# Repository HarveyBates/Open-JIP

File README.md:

### Description

Open-JIP is an open-source chlorophyll *a* fluorometer used to quantify photosynthetic phenotypes in terrestrial plants and microalgae. It is controlled via a Teensy microcontroller and features highly customisable electrical components and a 3D-printed infrastructure. 

#### OJIP

Open-JIP utilises a technique known as the fast polyphasic rise fluorescence
(also known as OJIP). Steady irradiance is provided from an emitting LED, this
excites photosynthetic antenna in the sample resulting in excess irradiance
being emitted as photons of a longer wavelength (i.e. fluorescence). The
emitted fluorescence, which contains information regarding the state of
photosynthesis, is captured by a photodiode, amplified by the custom circuitry
and stored by the Teensy microcontroller. This all happens in less than a second.

The transient captured by Open-JIP gives the user an indication of the state of photosynthesis in the subject organism to varying levels of complexity. If you would like to know more about the theory surrounding the measurement of chlorophyll *a* fluorescence, this [link](https://doi.org/10.1016/j.algal.2020.102105) gives a basic introduction and resources for further reading.

### Publication

The original device which used an Arduino Mega was published in [Photosynthesis Research in 2019](https://doi.org/10.1007/s11120-019-00673-2):

*A guide to Open-JIP, a low-cost open-source chlorophyll fluorometer - Bates et al. 2019*

If you would like to see what the device is capable of, you may be interested in this recent [publication](https://doi.org/10.1016/j.algal.2020.102105) which uses Open-JIP as a flow-through chlorophyll *a* fluorometer connected [a custom photobioreactor](https://github.com/HarveyBates/Phenobottle) with the microalga *Chlorella vulgaris*.

### Collaborations and custom architecture 

If you would like to collaborate on a project, or would like to see if Open-JIP can be customised to suit your application, please email me at [harvey_bates@hotmail.com](mailto:harvey_bates@hotmail.com). 

### Disclaimer

Open-JIP requires some knowledge of electronics, programming and photosynthesis to operate. If you have problems with the device place an issue in the [issues](https://github.com/HarveyBates/Open-JIP/issues) tab of this repository and I will do my best to address it as soon as possible.

# USER MANUAL

Below contains the user manual for Open-JIP, if you have any questions there is a discussions tab in this github repository, where I will do my best to get back to you as soon as possible.

## Contents

1. Introduction
   1. Specifications
   2. Getting started
      1. Downloading files
         1. Method 1 (New users)
         2. Method 2 (Experienced users / collaborators)
      2. Gathering materials
         1. Printed circuit board (PCB)
            1. Ordering a PCB
         2. 3D models
         3. Additonal parts
2. Firmware / Software
   1. Introduction
   2. Arduino IDE / Teensyduino
   3. Basic operations
      1. Basic functions
      2. Advanced functions
      3. Calibration functions
   4. Python control
   5. Advanced operations
      1. Change actinic LED intensity
      2. Change detection sensitivity
      3. Set analog reference voltage & Resolution
      4. Defaults
      5. Length of actinic pulse
3. Hardware
   1. Detection
      1. Gain adjustment 
   2. Actinic Intensity

## 1. Introduction

### Specifications

| Feature            | Value / Description                                          |
| ------------------ | ------------------------------------------------------------ |
| Actinic LED Colors | **Blue** 455 – 485 nm (466 nm), **Green** 517 – 555 nm (532 nm), **Orange** 583 – 600 nm (593 nm), **Red** 617 – 635 nm (626 nm). |
| Resolution         | 10 to 16-bit (optimised for 12-bit)                          |
| Sampling rate      | 8 &mu;s at 12-bits                                           |
| Operating voltage  | 15 V 1.2 A (Barrel plug)                                     |
| Communications     | USB (Serial)                                                 |
| Microcontroller    | Teensy 3.5/3.6 or Teensy 4.1 (3.6 Recommended)               |
| Actinic Intensity  | Four intensities (Low, Mid, High, Very High)                 |
| Detection (Gain)   | Four settings (Low, Mid, High, Very High)                    |

### Getting started

#### Downloading files

##### Method 1 (New users)

New users should navigate to the [releases](https://github.com/HarveyBates/Open-JIP/releases) page to find the most recent (and stable) version of the device. You can download the latest release as a `.zip` file and this will contain all the files you need to get the device up and running. 

The most recent version is **v0.3**. 

When searching through files in this repository all relevant folders are labeled with a specific version. You will want to use files that match the version you are using.

##### Method 2 (Experienced users / collaborators)

If you want to contribute to the project or fork this directory feel free to do so, just know that I constantly update files here so they may not function as expected before release. 

To clone this directory type this into your terminal / console.

```bash
git clone https://github.com/HarveyBates/Open-JIP.git
```

#### Gathering materials

Open-JIP can be built in an afternoon if you have all the equipment at hand. The folder "Bill of Materials" contains all the materials needed to build Open-JIP. This has been divided into two parts; (1) circuit board and (2) other. 

In addition to the Bill of Materials you will need to have access to:

1. A soldering iron
2. Solder (Paste or wire variety)
3. A re-flow oven (not necessary but makes the circuit board easier to assemble)
4. A 3D-printer
5. A pair of wire strippers / cutters
6. Some tweezers

##### Printed circuit board (PCB)

In the ```Bill of Materials/Circuit Board``` folder you will find a table all the components needed to construct the Open-JIP circuit board. These components can be bought from common electronics suppliers such as [digikey](https://www.digikey.com/), [LCSC](https://lcsc.com/en) or [farnell](https://au.element14.com/) etc. Links for each component is provided.

Note that most of the components are surface mount (SMD), this is due to their increased reliability and in my opinion its easier to assemble SMD compared to through-hole (THT) components. 

###### Ordering a PCB

To order the circuit board I recommend using [JLCPCB](https://jlcpcb.com/) as they are cheap, easy and ship fast. 

1. Open the folder titled Electronics 
2. Navigate to your current version 
3. In the subdirectory select the folder containing gerber and drl files
4. Compress this folder into a ```.zip``` file. 
5. On the JLCPCB website drag and drop the ```.zip``` file into the order form. 

The default settings are suitable. 

##### 3D Models

The 3D-models used for 3D-printing Open-JIP can be found in the ```Open-JIP/Hardware``` folder. Two file types are specified:

1. ```.stl``` can be directly imported into 3D-printing software such as [Ultimaker-Cura](https://ultimaker.com/software/ultimaker-cura) or sent to a local 3D-printing manufacturer.
2. ```.STEP``` is the modifiable Open-JIP 3D-model and as such can be configured whichever way you want before being exported as a ```.stl``` file. You can use 3D modeling software to do this such as [Fusion360](https://www.autodesk.com/products/fusion-360/overview) or [Solidworks](https://www.solidworks.com/).

##### Additional parts

In addition to the above electronics you will need a few components such as a Teensy microcontroller, power supply, computer to use the device etc. A table of all these additional items can be found in the folder location ```Bill of Materials/Other```.

## 2. Firmware / Software

### Introduction

Open-JIP operates via a computers serial port (USB connection), the user sends commands in the form of strings that are read by the Teensy microcontroller. This results in the device taking a measurement or other tasks. You can do this manually though the Arduino IDE or by using scripts in various languages. 

### Arduino IDE / Teensyduino

To setup the Teensy (upload the firmware to the microcontroller) you will need **both** [Arduino IDE](https://www.arduino.cc/en/software) and [TeensyDuino](https://www.pjrc.com/teensy/teensyduino.html) if running on Linux or Windows, or just [TeensyDuino](https://www.pjrc.com/teensy/teensyduino.html) if using a Mac. Instructions on how to do this is provided in the above links. 

When first using Open-JIP: 

1. Plug the Teensy into your computer
2. Open Arduino IDE
3. Select ```Tools>Board>Teensy 3.6``` (may be in another part called Teensyduino)
4. Select ```Port>"Your Teensy Device"```
5. ```File>Open``` the "Teensy.ino" file found in ```Firmware/v0.3/Teensy_3.6/Teensy_3.6.ino```
6. ```Sketch>Upload``` to flash the file onto the Teensy

The provided ```Teensy.ino``` file will work as is, but if you wish to change settings in this file you will need to reupload the firmware to the Teensy again after changes have been made.

### Basic Operations

To take a measurement open the serial monitor (in the Arduino IDE when the device is connected to your computer) (```Tools>Serial Monitor```) and type in the command ```MF``` (denoting **m**easure **f**luorescence). This will (in the default configuration) take a one second measurement of chlorophyll *a* fluorescence and print the resulting measurements out into the serial monitor. You can copy and paste the data into excel in order to graph the transient.

There are a number of included functions that require the same method to operate:

#### Basic functions

1. ```MF``` - **M**easure fluorescence. Measure the chlorophyll *a* fluorescence signature of the organism of interest. 
2. ```CP``` - **C**alculate **p**arameters. Calculate and print out basic fluorescence parameters from the most recent OJIP curve. 
3. ```CFo``` - **C**alibrate **F<sub>o</sub>** (the minimum level fluoresence). Provides short flashes of illumination for calibrating the minimum level fluorescence. This command is useful if you want to know if your measurement is going to *saturate* (due to an overly concentrated sample) before taking a measurement. 
4. ```An``` - **A**ctinic intensity (irradiance of LED) where *n* is a number between 1 and 4 (lowest to highest).
5. ```Fn``` - **F**luorescence gain (sensitivity of detection) where *n* is a number between 1 and 4 (lowest to highest).

**Note** - It is recommended that the minimum level of fluorescence (F<sub>o</sub>) is greater than 0.3 V for the maximum stability of acquisitions.

#### Advanced functions

1. ```MJ``` - **M**easure **J**-step. Measures up to the J-step (~2 ms) and returns the data to the serial port.
2. ```MW``` - **M**easure **w**ave. Measures up to the J-step multiple times with set time intervals between acquisitions. 

#### Calibration functions

1. ```ML``` - Calibrate actinic intensity (**m**easure **l**ight). Turns on the actinic LED for a period of three seconds to allow the intensity to be measured by a 4&#960; light meter.
2. ```Cr``` **C**alibrate **r**ise time of the actinic LED/amplifier combination. Provides some short  (100us) flashes of illumination from the actinic LED to calibrate your setup using an external oscilloscope. Useful if you want to ensure your Fo value is accurate (i.e. Fo should be measured when the actinic LED and amplifier are stable (usually around 40us)). *Note* this is only nessesary if you alter the default electronics configuration (see below).  

### Python Control

Open-JIP comes with an external cross platform python script that allows users to take basic measurements, plot the data and sort it into a ```.csv``` file automatically. This program is located under ```External Control/Open-JIP.py```.

```Open-JIP.py``` uses [plotly](https://plotly.com/python/) to plot the data and [pyserial](https://pyserial.readthedocs.io/en/latest/pyserial.html) to access the serial port of your machine. You must have [python](https://www.python.org/) installed to use this script. **This program runs in the terminal / console**. Additonally you need pip to install these requirements as follows:

```bash
cd Open-JIP/Software
pip3 install -r requirements.txt
python3 Open-JIP.py
# or (depending on python installation)
pip install -r requirements.txt
python Open-JIP.py
```

If you wish to change the output path of the ```.csv``` file you can do so by changing this string in ```Open-JIP.py```:

```python
fileName = "Open-JIP_Data.csv"  # Filename of output .csv file
```

### Advanced operations

A major feature of Open-JIP is its customisability. In the firmware users can adjust:

1. The actinic LED intensity
2. The detection sensitivity
3. The analog reference voltage
4. Resolution of the device
5. Length of actinic pulse

This next section is going to be in reference to the files located within ```Firmware/v0.3/Teensy_3.6```.

#### Change actinic LED intensity

In ```actinic.cpp``` the actinic LED intensity can be adjusted. There are four possible configurations, LOW, MID, HIGH, VERY HIGH. These can be selected by applying the values 1 - 4 (LOW - VERY HIGH) when switching on the actinic LED. 

```C++
void Actinic::on(){
  switch(intensity){
    case 1:
      digitalWrite(actinicGain1, HIGH); // Low
    	break;
    case 2:
      digitalWrite(actinicGain2, HIGH); // Mid
      break;
    case 3:
      digitalWrite(actinicGain3, HIGH); // High
      break;
    case 4:
      digitalWrite(actinicGain4, HIGH); // Very high
      break;
  }
}
```

*Note-* Electrical components have intrinsic variability. If using identical devices ensure actinic intensity is similar using a PAR meter.

*DO NOT -* combine actinic LED intensities as this will result in undefined behaviour. 

#### Change detection sensitivity

In ```sensitivity.cpp``` the detection sensitivity can be adjusted. There are four possible detection configurations, LOW, MID, HIGH, VERY HIGH (1 - 4). These are set before starting an exposure for stability and are therefore defined by the user.

```C++
void Sensitivity::define(int _gain){
    refresh();
    switch(_gain){
        case 1:
            // Lowest
            digitalWrite(fluoroGain1, HIGH); // Photosynthesis (OJIP)
            break;
        case 2:
            digitalWrite(fluoroGain2, HIGH); // Photosynthesis (OJIP)
            break;
        case 3:
            digitalWrite(fluoroGain3, HIGH); // Concentration only (not recommended for photosynthesis)
            break;
        case 4:
            // Highest
            digitalWrite(fluoroGain4, HIGH); // Concentration only (not recommended for photosynthesis)
            break;
    }
}
```
**NOTE**

Recent testing of the gain settings of Open-JIP has led to the conclusion that the current version of the device (v0.3) can only use gain 1 and 2 for photosynthesis (OJIP) measurements. Gain 3 and 4 should only be used for concentration estimates using the fluorescence intensity at ~120 &mu;s.

 *DO NOT* - combine gain settings as this will result in undefined behaviour. 

#### Set analog reference voltage & Resolution

In ```fluorescence.cpp``` the reference voltage can be adjusted to either 3.3 or 1.1 volts when using a Teensy 3.6. The purpose of this is (1) the Teensy 3.6 (1.1 V) reference voltage is more stable than 3.3 V and (2) you can attain a higher resolution when measuring weak fluorescence signals.

```C++
void Fluorescence::set_reference_voltage(float voltage){
  // Sets and initialises the required reference voltage for measurements
  if(voltage == 3.3){
    analogReference(DEFAULT); // Set to 3.3 V
  }
  else if(voltage == 1.1){
    analogReference(INTERNAL1V1); // Set to 1.1 V
  }
  else{
    analogReference(DEFAULT); // Set to default (3.3 V) if unknown value is found
  }
  analogRead(readPin); // Initialise reference voltage
}
```

*Note* - This is usually done statically at the start of the program by adjusting the value of ```refVoltage``` to either 3.3 or 1.1 depending on your requirements.

The number of bits for each reading can be changed via this command in the ```void setup()``` function:

```c++
analogResolution(12); // 12-bit resolution
```

*Note* - **Increasing** the resolution **decreases** the sampling rate so if you want to get alot of data points around Fo I reccomend you use a 12 or 10-bit resolution.

If you use have a 12 bit-resolution with a reference voltage of 1.1V the finest sensivitiy of the device is 0.00027 V per-division (1.1V / 2<sup>12</sup>) at a 8 &mu;s sampling rate. 

#### Defaults

Upon startup, Open-JIP will revert to its default configuration. You can change this by altering the setup command in ```Teensy_3.6.ino```:

```C++
void setup() {
  Serial.begin(115200); // Starting baud rate
  analogReadResolution(12); // Default resolution
  pinMode(13, OUTPUT); // Sets the microcontrollers LED pin as an output
  
  sensitivity.refresh(); // Switch off all sensitivity settings
  sensitivity.define(1); // Set a default sensitivity (1 - 4)

  actinic.off(); // Switch off all actinic settings
  actinic.define(1); // Set a default actinic irradiance (1 - 4)
}
```

#### Length of actinic pulse

In ```fluorescence.h``` the length of the actinic exposure (pulse) can be adjusted. The acquisition is done in two steps; (1) the fast measurments (readings every 8 &mu;s) and (2) slow (readings every 1 ms). These arrays require different processing methods and are therefore stored seperately. Below gives you an idea of how the array lengths are calculated for the intial aqusitions and the converted output. 

```c++
// Microsecond (micro) = readings every 8 us
static const unsigned int microLength = 1000; 
int microRead [microLength];
int milliRead[microLength];

// Millisecond (milli) = readings every 1 ms
static const unsigned int milliLength = 1000; 
int microTime[milliLength]; 
int milliTime[milliLength];

// Stores final array in converted form (i.e. Volts and Milliseconds)
float fluorescenceValues[microLength + milliLength];
float timeStamps[microLength + milliLength];
```

*Note* - If you are using the ```Open-JIP.py``` script you will need to change the number of data points that are read to match the length of ```fluorescenceValues```:

```python
timeStamps, fluorescenceValues = measure_fluorescence(2000) # Match with teensy script array length (default 2000)
```

## 3. Hardware

Open-JIP operates using a Teensy 3.6 microcontroller connected to a custom printed circuit board (PCB). The circuit is divided into two parts:

1. Detection - Responsible for detecting emitted fluorescence
2. Actinic intensity - Responsible for turning on and off the actinic LED

### Detection

Fluorescence detection is achieved with the use of an operational amplifier (op-amp) connected as a transimpedance amplifier. The inverting input is connected to a photodiode, while the non-inverting input is connected to a voltage divider to provide a very small offset voltage. The concept of the offset voltage is that the amplifier (op-amp) will respond faster to changes in voltage. 

*Note-* Resistor values may change depending on your application.

#### Gain adjustment

Four different sensitivities are provided though the use of a CMOS switch (74HC4066D) which has a range of different feedback resistors (1M, 2M, 3.3M and 3.9M). These resistors are all 0805 SMD. The gain is selected in the firmware of Open-JIP; however, if you wish to adjust the senstivity futher you can do so by changing one or more of these resistors. 

**Increasing** the resistance of the feedback resistor will **increase** the sensitivty of detection.

**Decreasing** the resistance of the feedback resistor will **decrese** the sensitivty of detection.

**Note**

Feedback resistances above 2Mohm are not suitable for OJIP measurements in v0.3. Ideally the feedback resistor should be a small as possible to increase the response time of the device.

**Note**

If you begin to get a large overshoot occurring at the start of your measurements you may need to increase the capacitor value (C3) to 2pF - 5pF. This [article](https://wiki.analog.com/university/courses/electronics/electronics-lab-1st) may help you if you encounter this issue.

### Actinic intensity

The actinic LED is controlled in the same way as the detection circuit i.e. Using a CMOS switch to controll its brightness. Again four levels of brightness can be selected in the firmware and are controlled by resistors (10K, 12K, 15K, 20k) connected to the base of the darlington transisitor (BD681). Adjusting the value of these resistors will result in the LED getting brighter or dimmer based on their resistance value.

*Note-* Resistor values may change depending on your application.

The input voltage (15 V) is filtered through a 12 V linear voltage regulator. This regulator ensures the actinic LED is stable of the measurement. A small capacitor (C7 - 1 &mu;F) is placed across the LED's terminal to prevent overshoot. If you want the LED to respond faster you can reduce the value of this capacitor while using an oscilloscope to check the devices rise-time. 

**Increasing** the resistors results in **decreased** actinic brightness.

**Decreasing** the resistance of R10 results in **increased** actinic brightness.

**Note**

Gate resistor values are dependent on a number of factors including manufacturer tolerances and LED color. Dialing in the resistor values to use in your device is an important consideration. Typically you will need a PAR meter to calibrate the devices brightness before use (if using for OJIP measurements). However, if access to a PAR meter is an issue, the shape of the OJIP curve can be an indicator of LED intensity. If the rise between Fo and Fj is sharp and rapid (<2ms), typically the device has enough brightness to saturate the electron transport chain. However, if the rise between Fo and Fj is gradual (>2ms), the brightness may not be bright enough. 

## Future of Open-JIP

Since the publication of Open-JIP a number of changes have been made to increase the devices capabilities. These include:

1. ~~Adjustable fluorescence protocols~~

2. ~~Ability to change detection sensitivity dynamically (though software)~~

3. ~~Adjustment of actinic LED intensity dynamically (through software)~~
4. Improvements in resolution
5. Improvements in number of datapoints in each OJIP transient

## Licence

The software in this work is licensed under GNU AFFERO GENERAL PUBLIC LICENSE Copyright (C) (2020) (Harvey Bates)

This program is free software: you can redistribute it and/or modify it under the terms of the GNU General Public License as published by the Free Software Foundation, either version 3 of the License, or (at your option) any later version.

This program is distributed in the hope that it will be useful, but WITHOUT ANY WARRANTY; without even the implied warranty of MERCHANTABILITY or FITNESS FOR A PARTICULAR PURPOSE. See the GNU General Public License for more details.

You should have received a copy of the GNU General Public License along with this program. If not, see https://www.gnu.org/licenses/

For more information contact: [harvey_bates@hotmail.com](mailto:harvey_bates@hotmail.com)

The hardware (3D Models, Electronic Schematics) in this work is licensed under a [Creative Commons Attribution-ShareAlike 3.0 Unported License](http://creativecommons.org/licenses/by-sa/3.0/).

[https://doi.org/10.1016/j.algal.2020.102105]: 
[https://pyserial.readthedocs.io/en/latest/pyserial.html]:

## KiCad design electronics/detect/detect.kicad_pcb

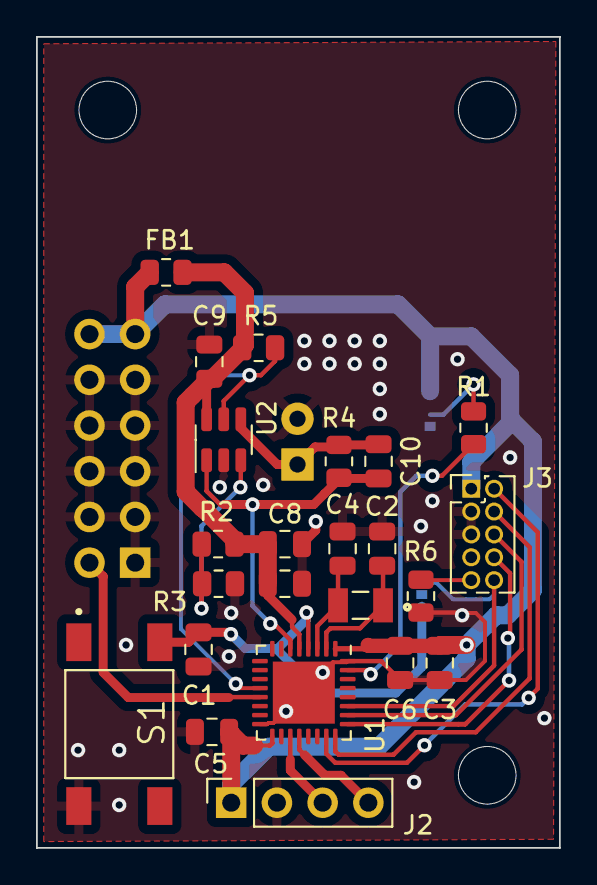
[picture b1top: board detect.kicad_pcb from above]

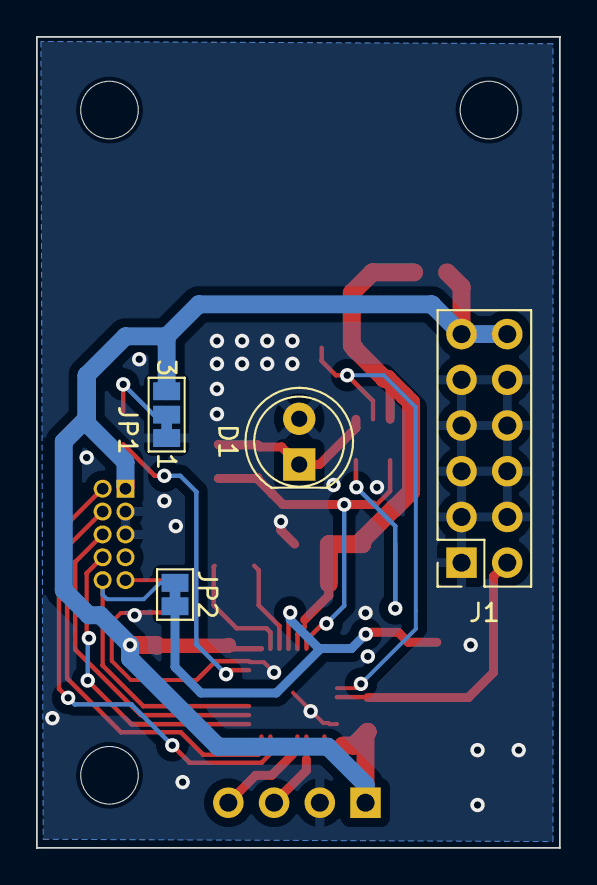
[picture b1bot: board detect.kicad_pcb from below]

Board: 2 copper layers, 29.1 x 45.1 mm, 27 parts (4 on the bottom side), 21 nets.

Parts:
C1, C3, C5, C9: 100nF; C_0805_2012Metric
C2, C4: 10pF; C_0805_2012Metric
C6: 4.7uF; C_0805_2012Metric
C7: 1uF; C_0805_2012Metric
C8: 10nF; C_0805_2012Metric
C10: 0.1pF; C_0805_2012Metric
D1: SFH213FA; LED_D5.0mm_IRGrey
FB1: R_0805_2012Metric
J1: Conn_02x06_Counter_Clockwise; PinSocket_2x06_P2.54mm_Vertical
J2: Conn_01x04_Socket; PinSocket_1x04_P2.54mm_Vertical
J3: Conn_ARM_JTAG_SWD_10; PinHeader_2x05_P1.27mm_Vertical
JP1: Boot_Sel; SolderJumper-3_P1.3mm_Bridged12_Pad1.0x1.5mm_NumberLabels
JP2: SolderJumper-2_P1.3mm_Bridged_Pad1.0x1.5mm
R1, R6: 10K; R_0805_2012Metric
R2: 1M; R_0805_2012Metric
R3: 33K; R_0805_2012Metric
R4: 500K; R_0805_2012Metric
R5: 100K; R_0805_2012Metric
S1: RESET; TL3301AF160QG
U1: STM32L432KCU6; QFN-32-1EP_5x5mm_P0.5mm_EP3.45x3.45mm
U2: OPA328DBVR; SOT-23-6
Y1: ECS-.327-12.5-34R-C-TR

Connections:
+3.3V: C3.1, C5.1, C6.1, FB1.2, J1.11, J1.12, J2.1, J3.1 (VTref), JP1.3 (B), U1.1 (VDD), U1.17 (VDD)
/ADC1_IN5: C10.2, R4.2, U1.6 (PA0), U2.1
/BOOT_SELECT: R1.2, U1.31 (PH3)
/PA6: R5.2, U1.12 (PA6), U2.5 (EN)
/PA7: J1.2, U1.13 (PA7)
/TCK/SWCLK_PA14: J3.4 (SWDCLK/TCK), U1.24 (PA14)
/TDI_PA15: J3.8 (NC/TDI), U1.25 (PA15)
/TDO/SWO_PB3: J3.6 (SWO/TDO), U1.26 (PB3)
/TMS/SWDAT_PA13: J3.2 (SWDIO/TMS), U1.23 (PA13)
/TRST_PB4: J3.10 (~RESET), JP2.1 (A), U1.27 (PB4)
/USART1_RX: J2.4, U1.20 (PA10)
/USART1_TX: J2.3, U1.19 (PA9)
GND: C1.2, C2.2, C3.2, C4.2, C5.2, C6.2, C7.2, C8.2, C9.2, D1.2 (A), J1.1, J1.3, J1.4, J1.5, J1.6, J1.7, J1.8, J1.9, J1.10, J2.2, J3.3 (GND), J3.5 (GND), JP1.1 (A), R3.2, R6.2, S1.2, U1.16 (VSS), U1.32 (VSS), U1.33 (VSS), U2.2 (V-)
NRST: C1.1, JP2.2 (B), S1.3, U1.4 (NRST)
unnamed: C10.1, D1.1 (K), R4.1, U2.4 (IN-)
unnamed: J3.9 (GNDDetect), R6.1
unnamed: JP1.2 (C), R1.1
unnamed: C2.1, U1.2 (PC14), Y1.1
unnamed: C4.1, U1.3 (PC15), Y1.2
unnamed: R2.2, R3.1, U2.3 (IN+)
VDDA: C7.1, C8.1, C9.1, FB1.1, R2.1, R5.1, U1.5 (VDDA), U2.6 (V+)

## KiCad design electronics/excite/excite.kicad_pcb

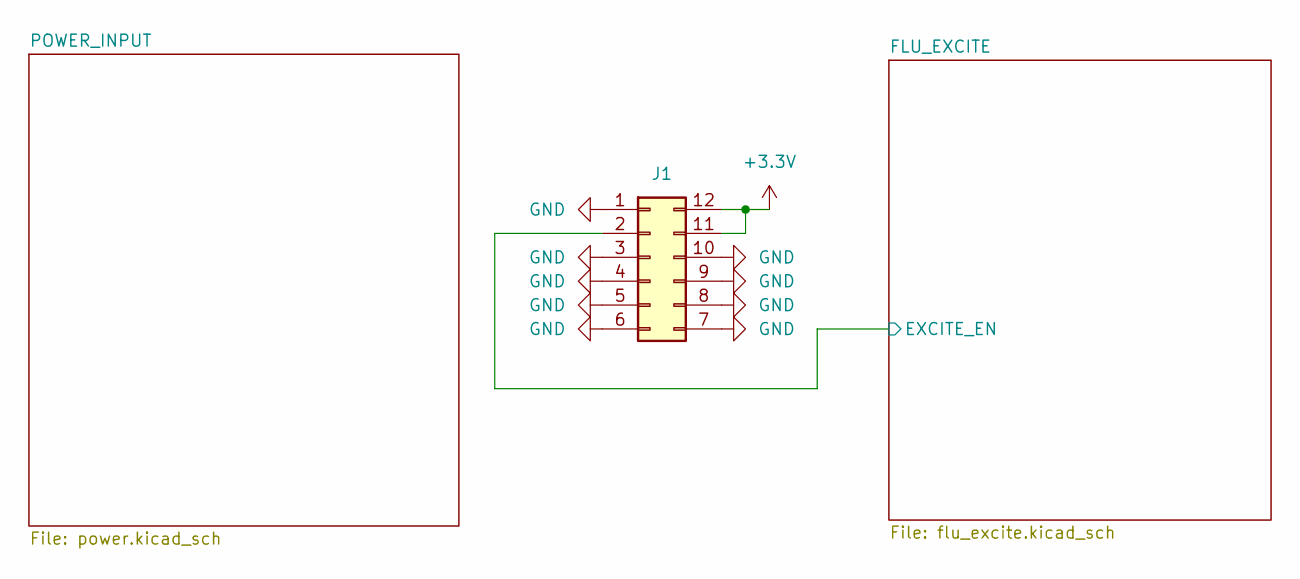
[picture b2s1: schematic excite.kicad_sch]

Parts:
J1: Conn_02x06_Counter_Clockwise; PinHeader_2x06_P2.54mm_Vertical

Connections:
+3.3V: J1.11, J1.12; also elsewhere on the board
/FLU_EXCITE/EXCITE_EN: J1.2; also elsewhere on the board
GND: J1.1, J1.3, J1.4, J1.5, J1.6, J1.7, J1.8, J1.9, J1.10; also elsewhere on the board

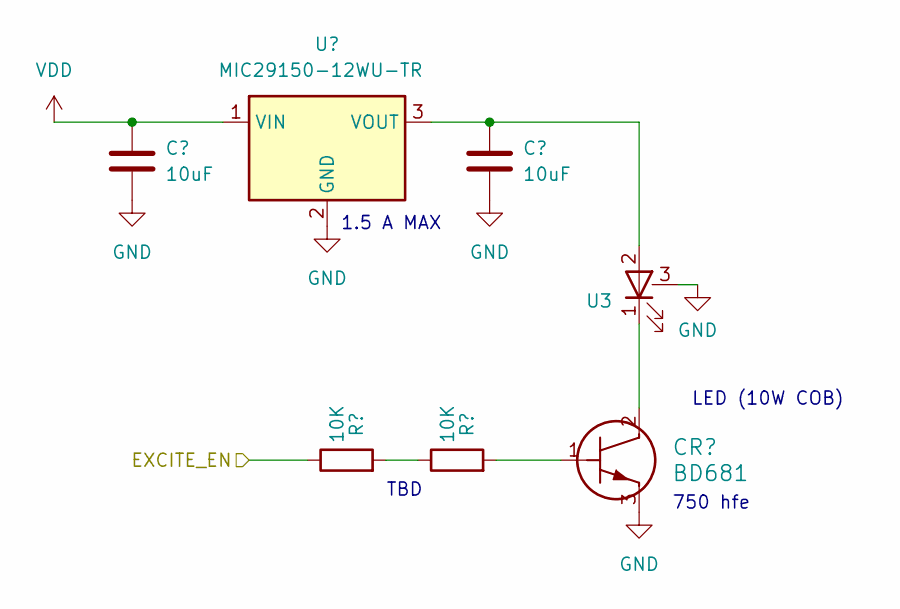
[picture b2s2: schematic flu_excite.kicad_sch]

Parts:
C5, C6: 10uF; CP_EIA-7343-15_Kemet-W; Part TAJD106K050RNJ
CR1: BD681
R2, R3: 10K; R_0805_2012Metric
U2: MIC29150-12WU-TR; MIC29150-12WU
U3: 10W_COB

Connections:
/FLU_EXCITE/EXCITE_EN: R2.1; also elsewhere on the board
GND: C5.2, C6.2, CR1.3, U2.2 (GND), U3.3; also elsewhere on the board
unnamed: CR1.1, R3.2
unnamed: CR1.2, U3.1
unnamed: R2.2, R3.1
unnamed: C6.1, U2.3 (VOUT), U3.2
VDD: C5.1, U2.1 (VIN); also elsewhere on the board

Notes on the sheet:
TBD
750 hfe
LED (10W COB)
1.5 A MAX

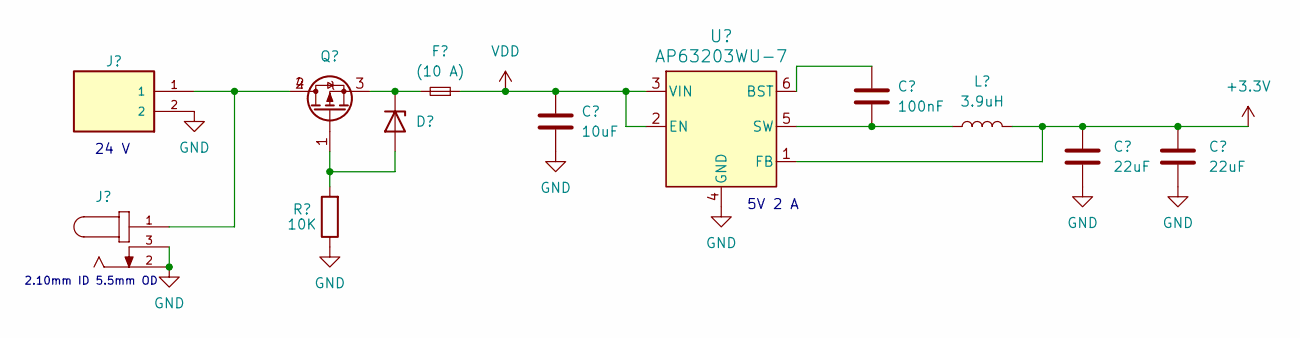
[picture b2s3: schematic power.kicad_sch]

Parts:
C1: 10uF; C_0805_2012Metric
C2: 100nF; C_0805_2012Metric
C3, C4: 22uF; C_0805_2012Metric
D1: D_Zener; MMSZ4700T1G
F1: (10 A); 0154010.DRL; Part 0154010.DRL
J2: TBP02R2-381-02BE
J3: PJ-002A
L1: 3.9uH; SDE0604A-3R9M; Part SDE0604A-3R9M
Q1: DMP6023LE-13
R1: 10K; R_0805_2012Metric
U1: AP63203WU-7; AP63205WU-7; Part AP63203WU-7

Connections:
+3.3V: C3.1, C4.1, L1.2, U1.1 (FB); also elsewhere on the board
GND: C1.2, C3.2, C4.2, J2.2, J3.2, J3.3, R1.1, U1.4 (GND); also elsewhere on the board
unnamed: D1.2 (A), Q1.1, R1.2
unnamed: D1.1 (K), F1.2, Q1.3
unnamed: J2.1, J3.1, Q1.2, Q1.4
unnamed: C2.1, U1.6 (BST)
unnamed: C2.2, L1.1, U1.5 (SW)
VDD: C1.1, F1.1, U1.2 (EN), U1.3 (VIN); also elsewhere on the board

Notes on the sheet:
24 V
5V 2 A
2.10mm ID 5.5mm OD

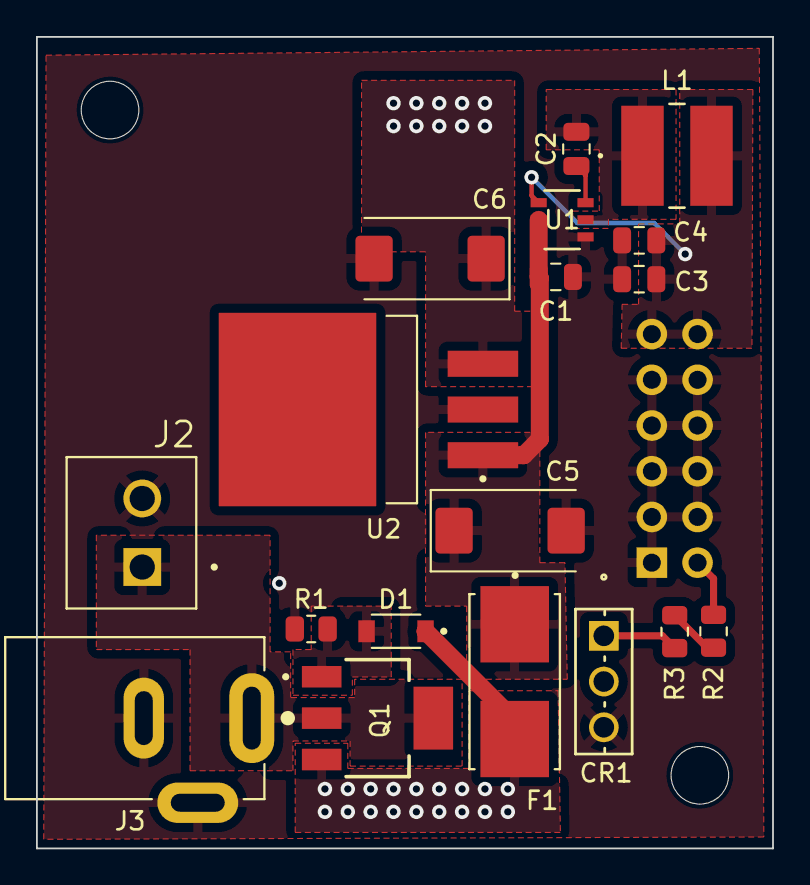
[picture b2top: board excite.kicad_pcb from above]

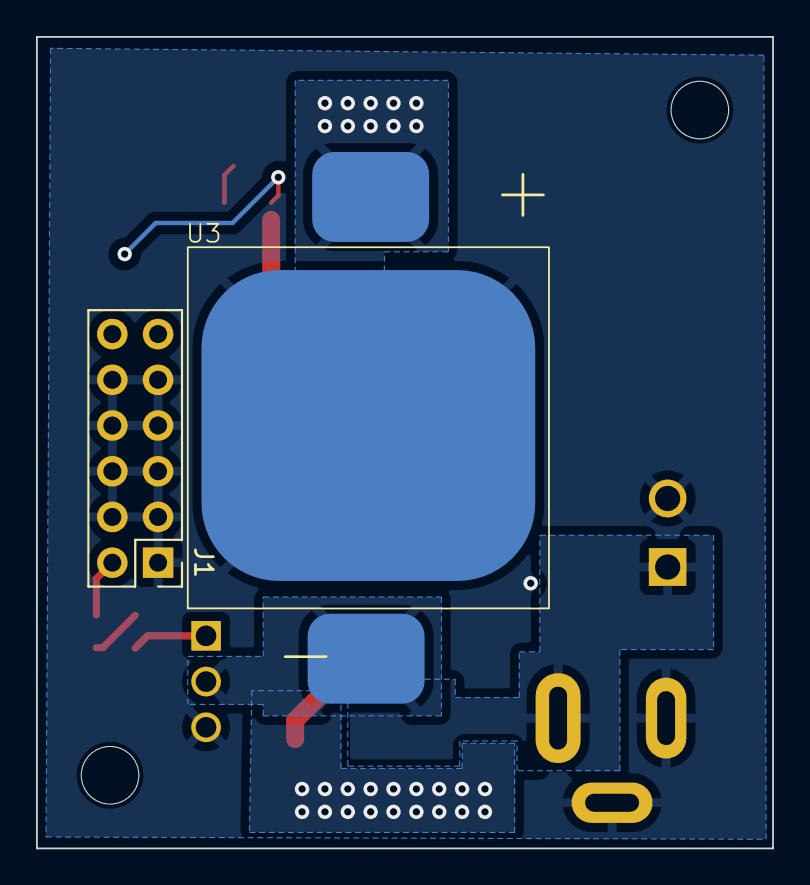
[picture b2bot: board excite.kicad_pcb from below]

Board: 2 copper layers, 40.9 x 45.1 mm, 20 parts (2 on the bottom side), 13 nets.

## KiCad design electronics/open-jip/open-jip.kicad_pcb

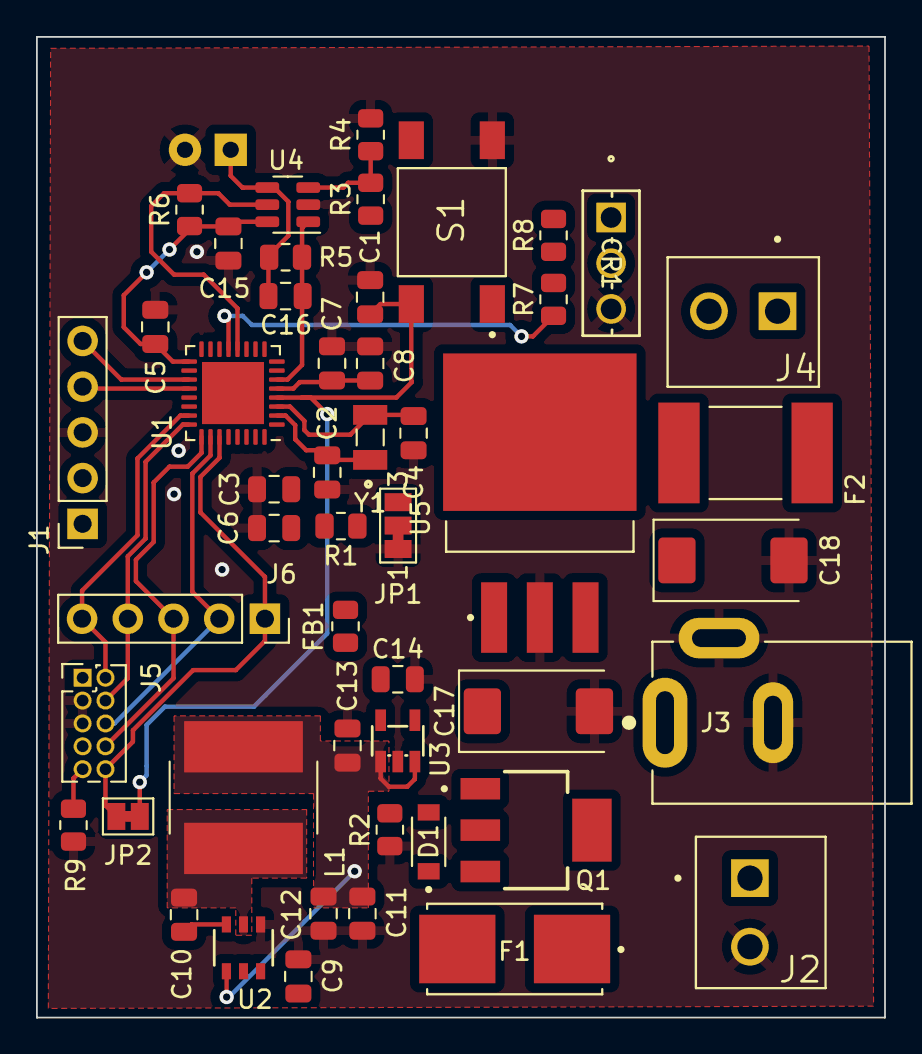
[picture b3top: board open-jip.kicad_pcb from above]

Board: 2 copper layers, 47.1 x 54.5 mm, 50 parts (1 on the bottom side), 33 nets.

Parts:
C1, C3, C5, C10, C15: 100nF; C_0805_2012Metric
C2, C4: 10pF; C_0805_2012Metric
C6: 4.7uF; C_0805_2012Metric
C7, C13, C14: 1uF; C_0805_2012Metric
C8: 10nF; C_0805_2012Metric
C9: 10uF; C_0805_2012Metric
C11, C12: 22uF; C_0805_2012Metric
C16: 0.1pF; C_0805_2012Metric
C17, C18: 10uF; CP_EIA-7343-15_Kemet-W
CR1: BD681
D1: D_Zener; MMSZ4700T1G
D2: SFH213FA; LED_D5.0mm_IRGrey
F1: (10 A); 0154010.DRL
F2: 1A; 0ZCF0100AF2A
FB1: R_0805_2012Metric
J1, J6: Conn_01x05_Socket; PinSocket_1x05_P2.54mm_Vertical
J2, J4: TBP02R2-381-02BE
J3: PJ-002A
J5: Conn_ARM_JTAG_SWD_10; PinHeader_2x05_P1.27mm_Vertical
JP1: Boot_Sel; SolderJumper-3_P1.3mm_Bridged12_Pad1.0x1.5mm_NumberLabels
JP2: SolderJumper-2_P1.3mm_Bridged_Pad1.0x1.5mm
L1: 4.7uH; L_Bourns_SRN8040TA
Q1: DMP6023LE-13
R1, R2, R7, R8, R9: 10K; R_0805_2012Metric
R3: 1M; R_0805_2012Metric
R4: 33K; R_0805_2012Metric
R5: 500K; R_0805_2012Metric
R6: 100K; R_0805_2012Metric
S1: RESET; TL3301AF160QG
U1: STM32L432KCU6; QFN-32-1EP_5x5mm_P0.5mm_EP3.45x3.45mm
U2: AP63205WU-7
U3: ADP122AUJZ-3.3-R7
U4: OPA328DBVR; SOT-23-6
U5: MIC29150-12WU
Y1: ECS-.327-12.5-34R-C-TR

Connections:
+3.3V: C3.1, C5.1, C6.1, C14.1, C15.1, FB1.2, J1.2, J5.1 (VTref), JP1.3 (B), R3.1, R6.1, U1.1 (VDD), U1.17 (VDD), U3.5 (VOUT), U4.6 (V+)
+5V: C11.1, C12.1, C13.1, J1.1, L1.2, U2.1 (FB), U3.1 (VIN), U3.3 (EN)
/ADC1_IN5: C16.2, R5.2, U1.6 (PA0), U4.1
/BOOT_SELECT: R1.2, U1.31 (PH3)
/PA6: R6.2, U1.12 (PA6), U4.5 (EN)
/PA7: R7.1, U1.13 (PA7)
/TCK/SWCLK_PA14: J5.4 (SWDCLK/TCK), J6.4, U1.24 (PA14)
/TDI_PA15: J5.8 (NC/TDI), J6.3, U1.25 (PA15)
/TDO/SWO_PB3: J5.6 (SWO/TDO), J6.2, U1.26 (PB3)
/TMS/SWDAT_PA13: J5.2 (SWDIO/TMS), J6.5, U1.23 (PA13)
/TRST_PB4: J5.10 (~RESET), J6.1, JP2.1 (A), U1.27 (PB4)
/USART1_RX: J1.4, U1.20 (PA10)
/USART1_TX: J1.5, U1.19 (PA9)
GND: C1.2, C2.2, C3.2, C4.2, C5.2, C6.2, C7.2, C8.2, C9.2, C11.2, C12.2, C13.2, C14.2, C15.2, C17.2, C18.2, CR1.3, D2.2 (A), J1.3, J2.2, J3.2, J3.3, J5.3 (GND), J5.5 (GND), JP1.1 (A), R2.1, R4.2, R9.2, S1.2, U1.16 (VSS), U1.32 (VSS), U1.33 (VSS), U2.4 (GND), U3.2 (GND), U4.2 (V-), U5.2 (GND)
NRST: C1.1, JP2.2 (B), S1.3, U1.4 (NRST)
unnamed: CR1.1, R8.2
unnamed: CR1.2, J4.2
unnamed: D1.2 (A), Q1.1, R2.2
unnamed: D1.1 (K), F1.2, Q1.3
unnamed: C16.1, D2.1 (K), R5.1, U4.4 (IN-)
unnamed: F2.2, J4.1
unnamed: J2.1, J3.1, Q1.2, Q1.4
unnamed: J5.9 (GNDDetect), R9.1
unnamed: JP1.2 (C), R1.1
unnamed: R7.2, R8.1
unnamed: C2.1, U1.2 (PC14), Y1.1
unnamed: C4.1, U1.3 (PC15), Y1.2
unnamed: C10.1, U2.6 (BST)
unnamed: C10.2, L1.1, U2.5 (SW)
unnamed: R3.2, R4.1, U4.3 (IN+)
unnamed: C18.1, F2.1, U5.3 (VOUT)
VDD: C9.1, C17.1, F1.1, U2.2 (EN), U2.3 (VIN), U5.1 (VIN)
VDDA: C7.1, C8.1, FB1.1, U1.5 (VDDA)

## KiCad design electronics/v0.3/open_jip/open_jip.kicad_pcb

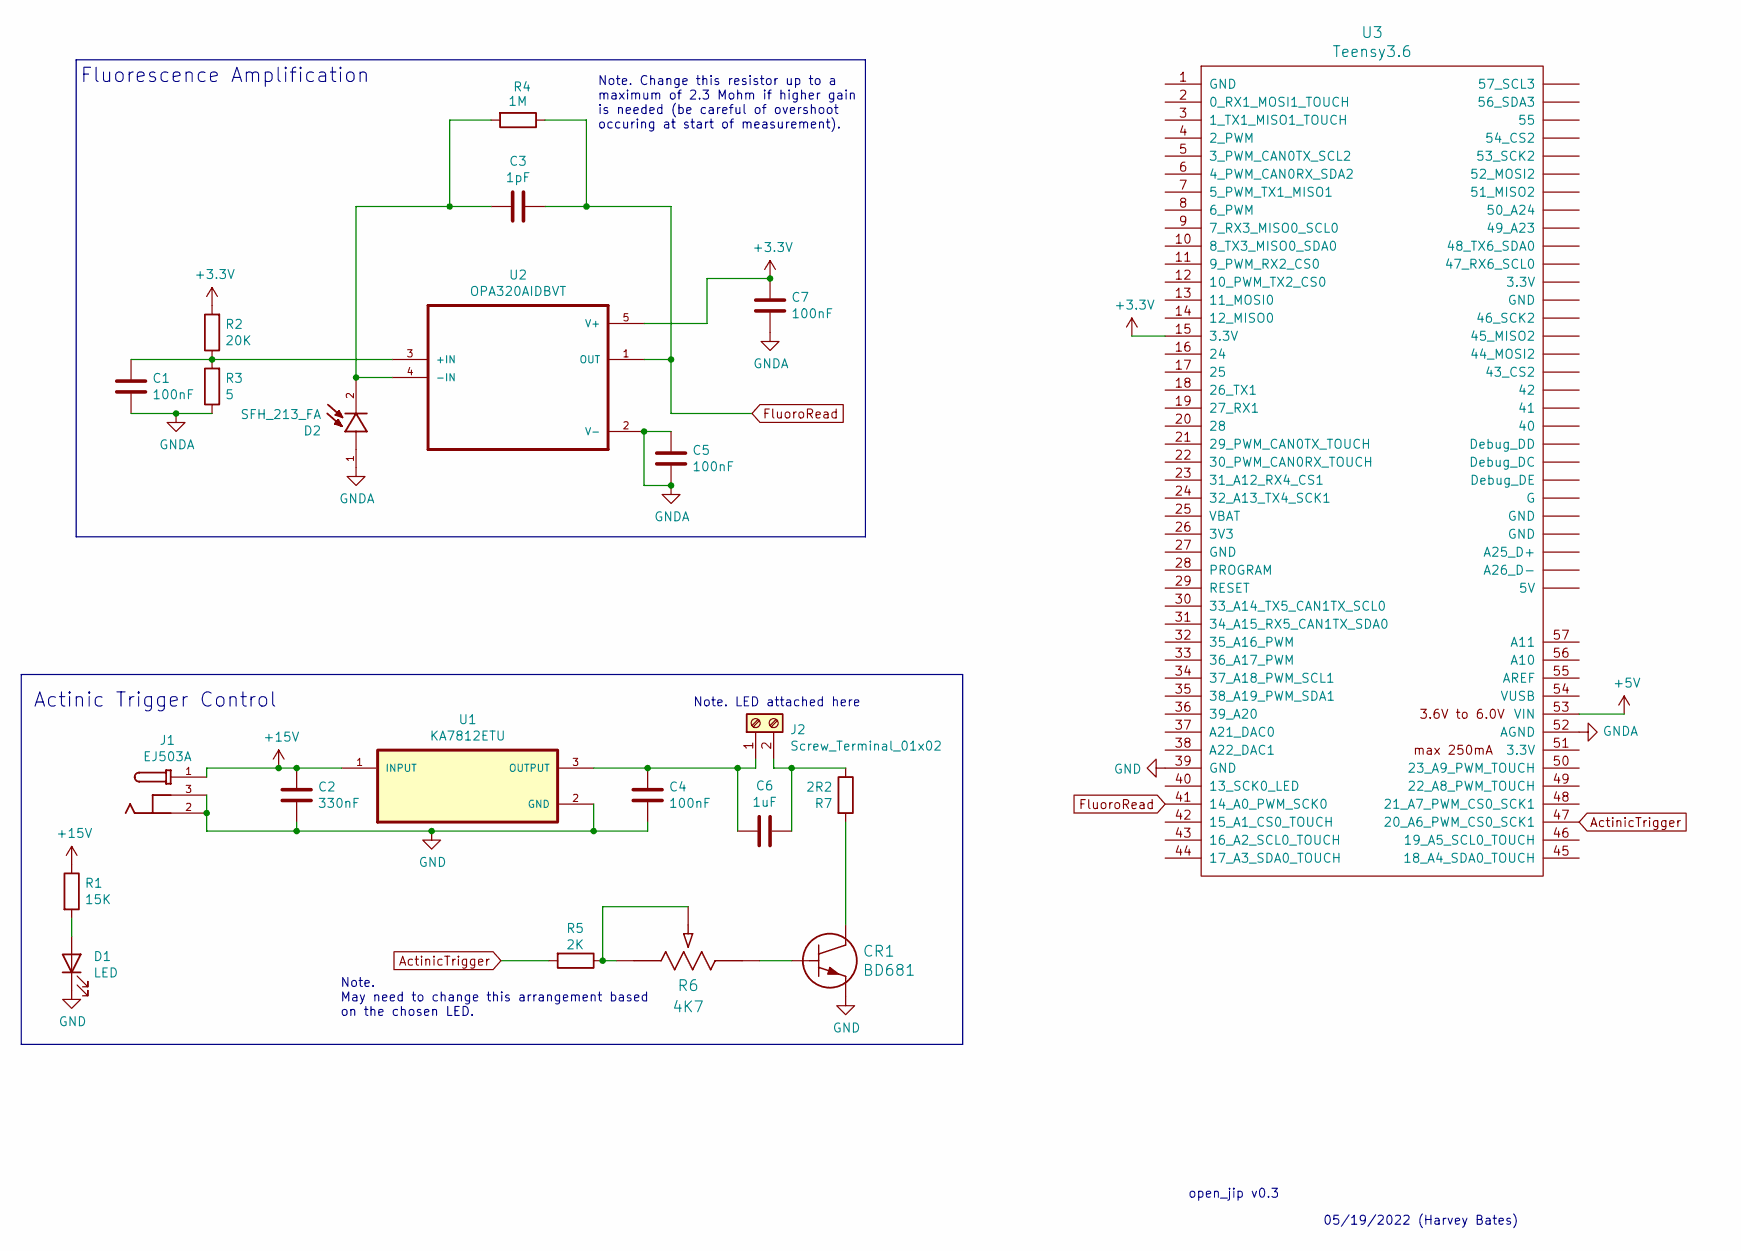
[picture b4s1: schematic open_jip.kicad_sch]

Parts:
C1, C4, C5, C7: 100nF; C_0805_2012Metric_Pad1.18x1.45mm_HandSolder
C2: 330nF; C_0805_2012Metric_Pad1.18x1.45mm_HandSolder
C3: 1pF; C_0805_2012Metric_Pad1.18x1.45mm_HandSolder
C6: 1uF; CP_Elec_4x5.4
CR1: BD681
D1: LED; LED_0805_2012Metric_Pad1.15x1.40mm_HandSolder
D2: SFH_213_FA; PARTREV 1.3
J1: EJ503A; PARTREV B
J2: Screw_Terminal_01x02; TerminalBlock_Altech_AK300-2_P5.00mm
R1: 15K; R_0805_2012Metric_Pad1.20x1.40mm_HandSolder
R2: 20K; R_0805_2012Metric_Pad1.20x1.40mm_HandSolder
R3: 5; R_0805_2012Metric_Pad1.20x1.40mm_HandSolder
R4: 1M; R_0805_2012Metric_Pad1.20x1.40mm_HandSolder
R5: 2K; R_0805_2012Metric_Pad1.20x1.40mm_HandSolder
R6: 4K7; 3386G-1-102LF
R7: 2R2; 35602R2JT
U1: KA7812ETU
U2: OPA320AIDBVT; OPA320AIDBVR
U3: Teensy3.6; Teensy35_36

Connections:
+3V3: C7.2, R2.2, U2.5 (V+), U3.15 (3.3V)
+5V: U3.53 (VIN)
+15V: C2.2, J1.1, R1.1, U1.1 (INPUT)
ActinicTrigger: R5.2, U3.47 (20_A6_PWM_CS0_SCK1)
FluoroRead: C3.1, R4.1, U2.1 (OUT), U3.41 (14_A0_PWM_SCK0)
GND: C2.1, C4.1, CR1.3 (E), D1.1 (K), J1.2, J1.3, U1.2 (GND), U3.39 (GND)
GNDA: C1.1, C5.1, C5.2, C7.1, D2.1, R3.1, U2.2 (V-), U3.52 (AGND)
unnamed: C1.2, R2.1, R3.2, U2.3 (+IN)
unnamed: C3.2, D2.2, R4.2, U2.4 (-IN)
unnamed: C4.2, C6.1, J2.1, U1.3 (OUTPUT)
unnamed: C6.2, J2.2, R7.1
unnamed: CR1.1 (B), R6.3
unnamed: CR1.2 (C), R7.2
unnamed: D1.2 (A), R1.2
unnamed: R5.1, R6.1, R6.2

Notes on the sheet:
Note. May need to change this arrangement based on the chosen LED.
05/19/2022 (Harvey Bates)
Fluorescence Amplification
Actinic Trigger Control
open_jip v0.3
Note. LED attached here
Note. Change this resistor up to a maximum of 2.3 Mohm if higher gain is needed (be careful of overshoot occuring at start of measurement).

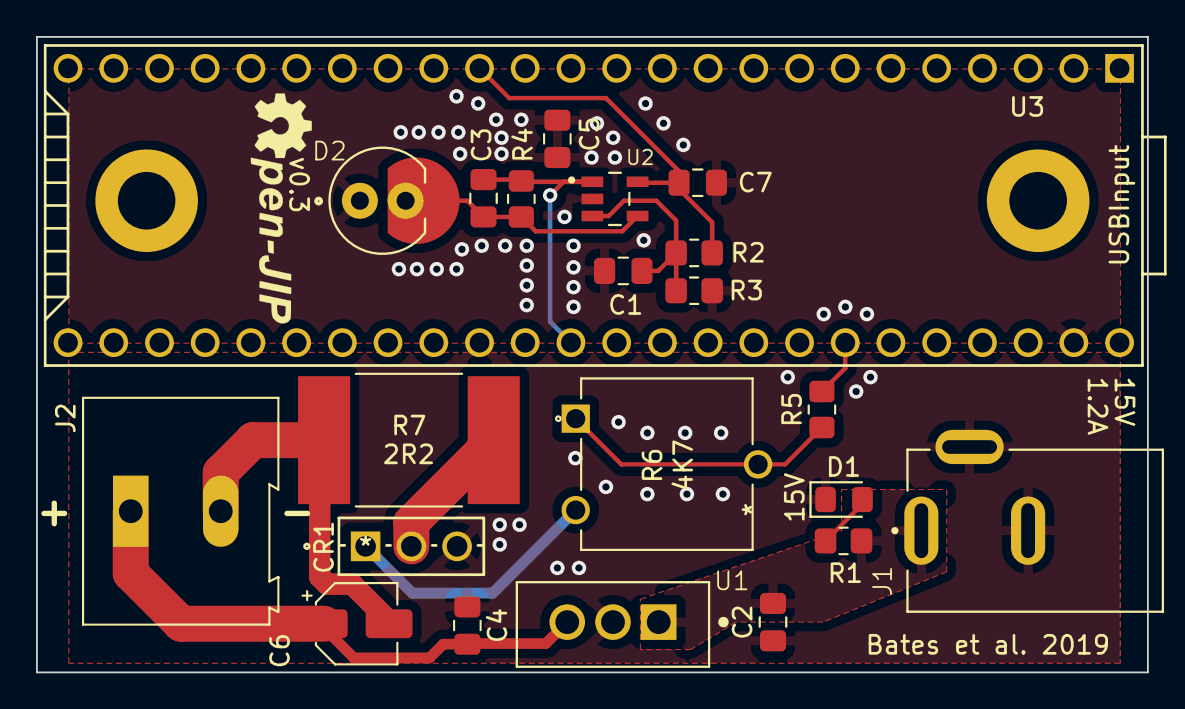
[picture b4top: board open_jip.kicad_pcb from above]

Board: 2 copper layers, 61.7 x 35.3 mm, 22 parts (0 on the bottom side), 14 nets.

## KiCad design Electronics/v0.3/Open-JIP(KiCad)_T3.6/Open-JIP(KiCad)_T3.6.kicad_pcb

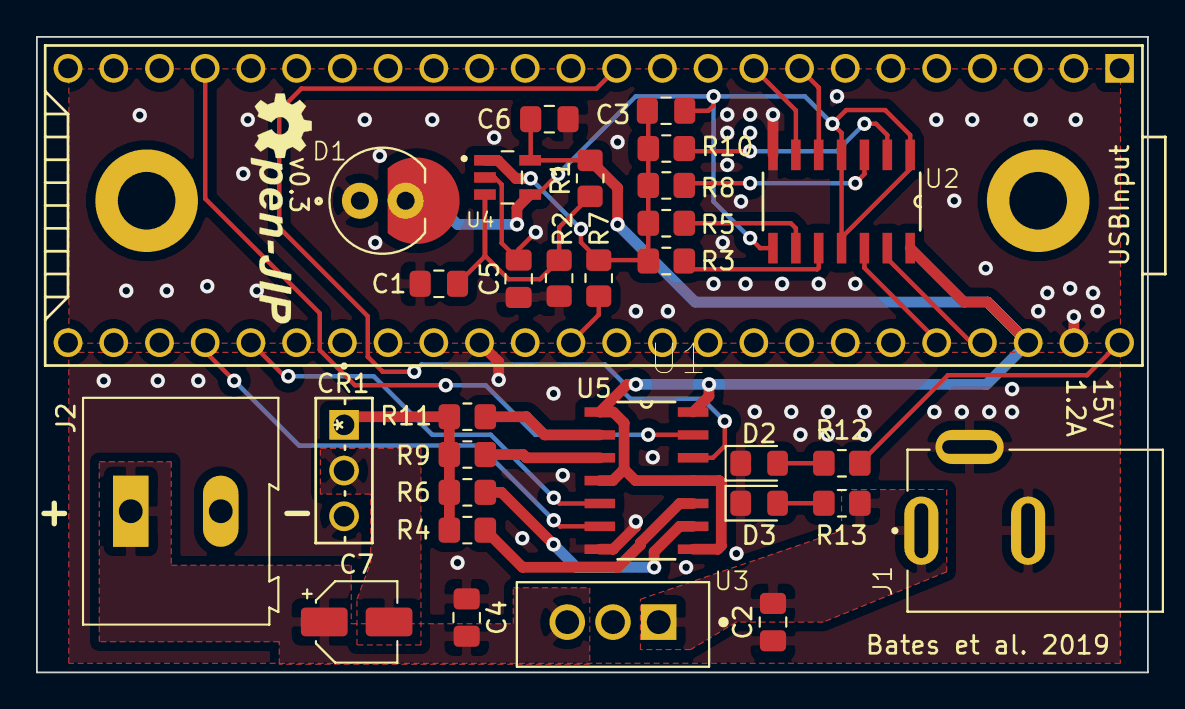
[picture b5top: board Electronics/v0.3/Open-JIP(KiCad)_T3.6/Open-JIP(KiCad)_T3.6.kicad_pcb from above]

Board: 2 copper layers, 61.7 x 35.3 mm, 31 parts (0 on the bottom side), 30 nets.

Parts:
C1, C4, C5, C6: 100nF; C_0805_2012Metric_Pad1.18x1.45mm_HandSolder
C2: 330nF; C_0805_2012Metric_Pad1.18x1.45mm_HandSolder
C3: 1pF; C_0805_2012Metric_Pad1.18x1.45mm_HandSolder
C7: 1uF; CP_Elec_4x5.4
CR1: BD681
D1: SFH_213_FA
D2, D3: LED; LED_0805_2012Metric_Pad1.15x1.40mm_HandSolder
J1: EJ503A; DCJack_MPD_EJ503A
J2: Screw_Terminal_01x02; TerminalBlock_Altech_AK300-2_P5.00mm
R1: 20K; R_0805_2012Metric_Pad1.20x1.40mm_HandSolder
R2: 5; R_0805_2012Metric_Pad1.20x1.40mm_HandSolder
R3: 3.9M; R_0805_2012Metric_Pad1.20x1.40mm_HandSolder
R4: 8.2K; R_0805_2012Metric_Pad1.20x1.40mm_HandSolder
R5: 3.3M; R_0805_2012Metric_Pad1.20x1.40mm_HandSolder
R6: 6.8K; R_0805_2012Metric_Pad1.20x1.40mm_HandSolder
R7: 47; R_0805_2012Metric_Pad1.20x1.40mm_HandSolder
R8: 2.3M; R_0805_2012Metric_Pad1.20x1.40mm_HandSolder
R9: 5.1K; R_0805_2012Metric_Pad1.20x1.40mm_HandSolder
R10: 1M; R_0805_2012Metric_Pad1.20x1.40mm_HandSolder
R11: 4.3K; R_0805_2012Metric_Pad1.20x1.40mm_HandSolder
R12: 1K; R_0805_2012Metric_Pad1.20x1.40mm_HandSolder
R13: 15K; R_0805_2012Metric_Pad1.20x1.40mm_HandSolder
U1, U2: 74HC4066D,653; SOIC127P600X175-14N
U3: KA7812ETU; TO253P1067X470X2040-3
U4: OPA320AIDBVT; SOT95P280X145-5N
U5: Teensy3.6; Teensy35_36

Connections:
+3V3: C6.2, R1.2, U1.1, U1.4, U1.8, U1.11, U1.14, U2.14, U4.5, U5.51
+5V: R12.1, U5.53
+15V: C2.2, J1.1, R13.1, U3.1
/-IN: C3.2, D1.2, U2.1, U2.4, U2.8, U2.11, U4.4
/Out: C3.1, R3.1, R5.1, R7.2, R8.1, R10.1, U4.1
/TrigOut: CR1.1, R4.1, R6.1, R9.1, R11.1
ActinicGain1: U1.13, U5.21
ActinicGain2: U1.5, U5.34
ActinicGain3: U1.6, U5.33
ActinicGain4: U1.12, U5.12
FluoroGain1: U2.13, U5.50
FluoroGain2: U2.5, U5.8
FluoroGain3: U2.6, U5.9
FluoroGain4: U2.12, U5.49
FluoroRead: R7.1, U5.41
GND: C2.1, C4.1, CR1.3, D2.1, D3.1, J1.2, J1.3, U1.7, U3.2, U5.39
GNDA: C1.1, C5.1, C5.2, C6.1, D1.1, R2.1, U2.7, U4.2, U5.52
unnamed: C1.2, R1.1, R2.2, U4.3
unnamed: C4.2, C7.1, J2.1, U3.3
unnamed: C7.2, CR1.2, J2.2
unnamed: D2.2, R12.2
unnamed: D3.2, R13.2
unnamed: R3.2, U2.10
unnamed: R4.2, U1.10
unnamed: R5.2, U2.9
unnamed: R6.2, U1.9
unnamed: R8.2, U2.3
unnamed: R9.2, U1.3
unnamed: R10.2, U2.2
unnamed: R11.2, U1.2

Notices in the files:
README.md:
Licence:
The software in this work is licensed under GNU AFFERO GENERAL PUBLIC LICENSE Copyright (C) (2020) (Harvey Bates)
CC BY-SA 3.0
The hardware (3D Models, Electronic Schematics) in this work is licensed under a [Creative Commons Attribution-ShareAlike 3.0 Unported License](http://creativecommons.org/licenses/by-sa/3.0/).
parts and their libraries:
Copyright 2021 Accelerated Designs. All rights reserved.
